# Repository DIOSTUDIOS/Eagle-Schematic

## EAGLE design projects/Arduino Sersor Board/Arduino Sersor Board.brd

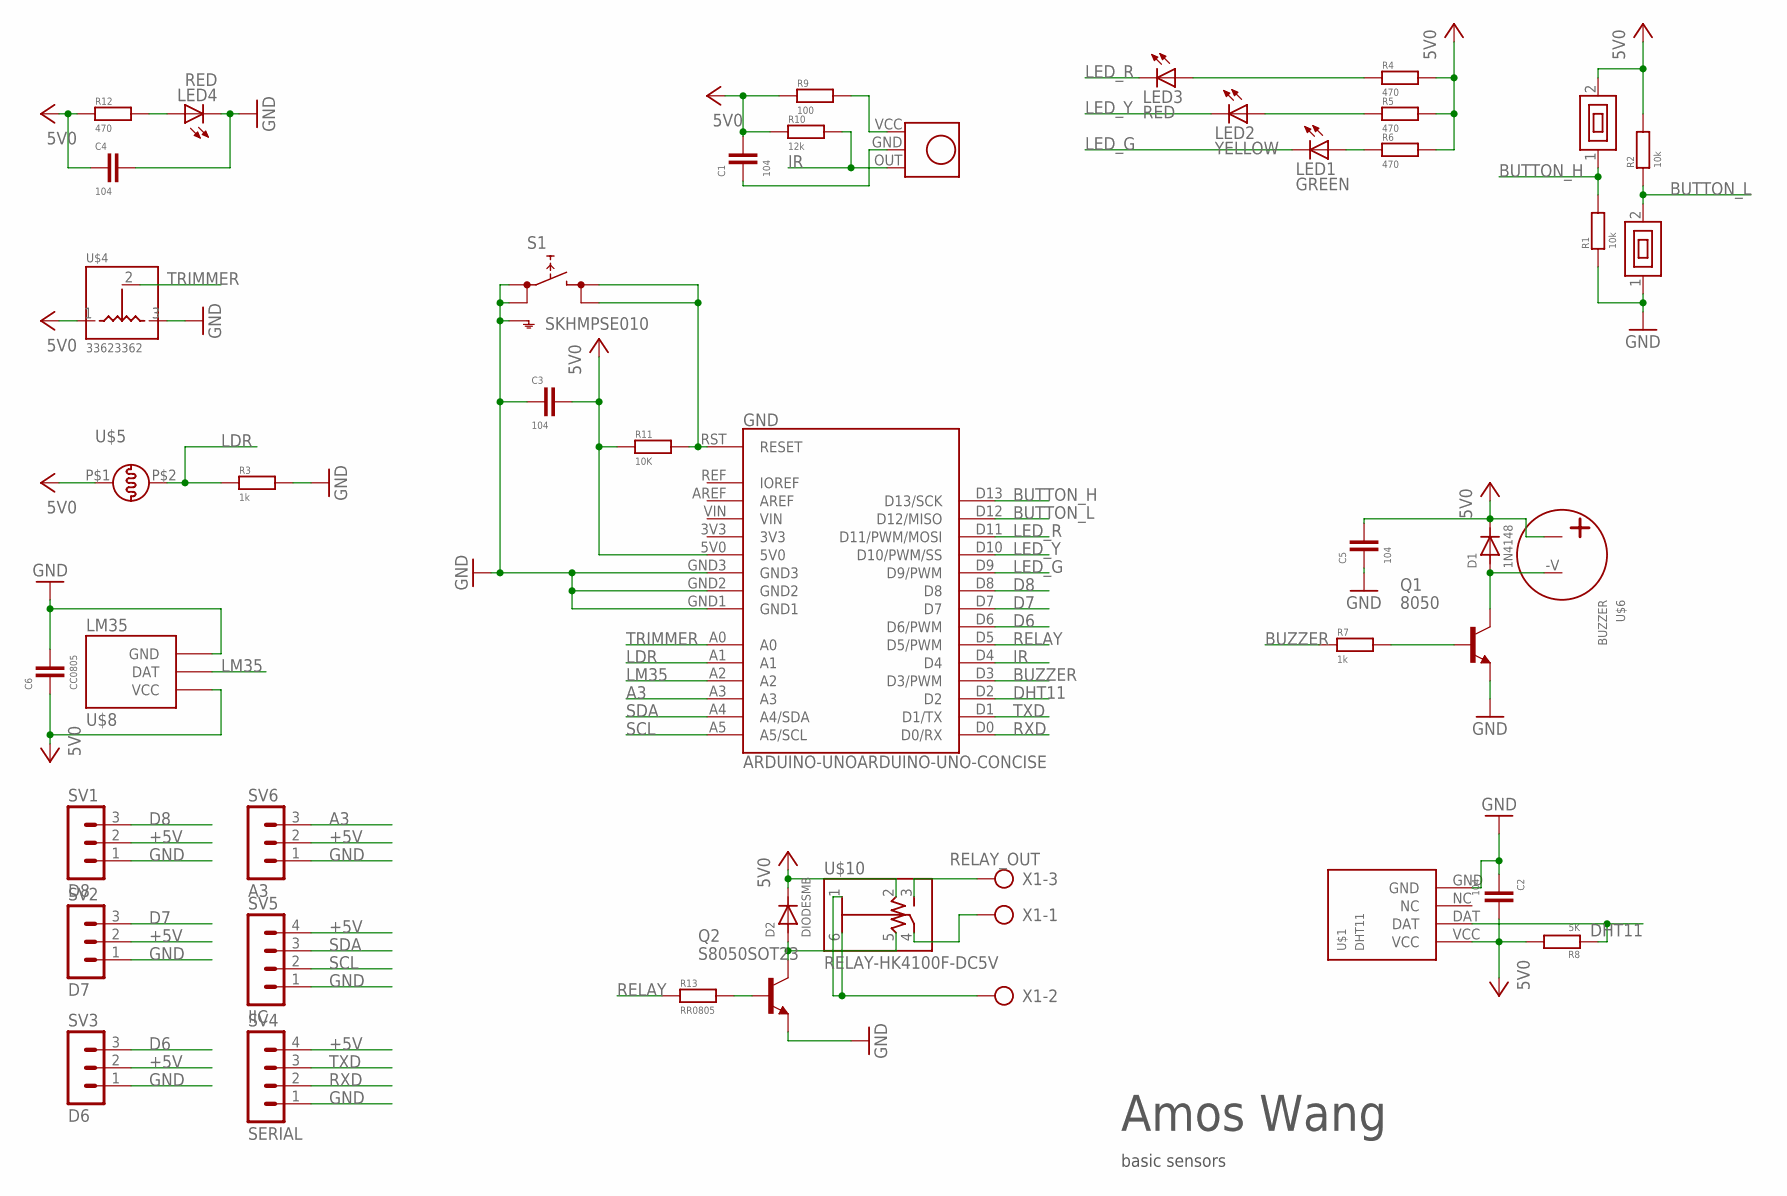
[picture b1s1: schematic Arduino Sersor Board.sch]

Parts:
C1, C2, C3, C4, C5: 104; C0805
C6: CC0805; C0805
D1: 1N4148; SMB
D2: DIODESMB; SMB
GND: ARDUINO-UNOARDUINO-UNO-CONCISE; ARDUINO-UNO
LED1: GREEN; LED2X5
LED2: YELLOW; LED2X5
LED3: RED; LED2X5
LED4: RED; CHIP-LED0805
Q1: 8050; SOT23
Q2: S8050SOT23; SOT23
R1, R2: 10k; R0805
R3, R7: 1k; R0805
R4, R5, R6, R12: 470; R0805
R8: 5K; R0805
R9: 100; R0805
R10: 12k; R0805
R11: 10K; R0805
R13: RR0805; R0805
S1: SKHMPSE010; SKHMPXE010
SV1: D8; MA03-1
SV2: D7; MA03-1
SV3: D6; MA03-1
SV4: SERIAL; MA04-1
SV5: IIC; MA04-1
SV6: A3; MA03-1
U$1: DHT11
U$2, U$3: SMD-36SMD-3*6; SMD-3*6
U$4: 33623362; 3362
U$5: LDR
U$6: BUZZER
U$8: LM35; TO92
U$9: IR-RECIEVER
U$10: RELAY-HK4100F-DC5V
X1: RELAY_OUT; AK500/3

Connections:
+5V: C1.1, C2.1, C3.1, C4.2, C5.1, C6.2, D1.1, D2.1, GND.5V0, R2.2, R4.2, R5.2, R6.2, R8.2, R9.1, R10.1, R11.1, R12.1, SV1.2, SV2.2, SV3.2, SV4.4, SV5.4, SV6.2, U$1.VCC, U$2.2, U$4.1, U$5.P$1, U$6.+V, U$8.1 (VCC), U$10.2
A3: GND.A3, SV6.3
BUTTON_H: GND.D13 (D13/SCK), R1.2, U$2.1
BUTTON_L: GND.D12 (D12/MISO), R2.1, U$3.2
BUZZER: GND.D3 (D3/PWM), R7.1
D6: GND.D6 (D6/PWM), SV3.3
D7: GND.D7, SV2.3
D8: GND.D8, SV1.3
DHT11: GND.D2, R8.1, U$1.DAT
GND: C2.2, C3.2, C4.1, C5.2, C6.1, GND.GND1, GND.GND2, GND.GND3, LED4.C, Q1.E, Q2.E, R1.1, R3.2, S1.1 (1.1), S1.2 (1.2), S1.5 (SH), SV1.1, SV2.1, SV3.1, SV4.1, SV5.1, SV6.1, U$1.GND, U$3.1, U$4.3, U$8.3 (GND)
IR: GND.D4, R10.2, U$9.OUT
LDR: GND.A1, R3.1, U$5.P$2
LED_G: GND.D9 (D9/PWM), LED1.K (C)
LED_R: GND.D11 (D11/PWM/MOSI), LED3.K (C)
LED_Y: GND.D10 (D10/PWM/SS), LED2.K (C)
LM35: GND.A2, U$8.2 (DAT)
unnamed: GND.RST (RESET), R11.2, S1.3 (2.1), S1.4 (2.2)
unnamed: LED4.A, R12.2
unnamed: LED3.A, R4.1
unnamed: LED2.A, R5.1
unnamed: LED1.A, R6.1
unnamed: Q1.B, R7.2
unnamed: D1.2, Q1.C, U$6.-V
unnamed: Q2.B, R13.2
unnamed: D2.2, Q2.C, U$10.5
unnamed: R9.2, U$9.VCC
unnamed: U$10.3, X1.3
unnamed: C1.2, U$9.GND
unnamed: U$10.4, X1.1
unnamed: U$10.1, U$10.6, X1.2
RELAY: GND.D5 (D5/PWM), R13.1
RXD: GND.D0 (D0/RX), SV4.2
SCL: GND.A5 (A5/SCL), SV5.2
SDA: GND.A4 (A4/SDA), SV5.3
TRIMMER: GND.A0, U$4.2
TXD: GND.D1 (D1/TX), SV4.3

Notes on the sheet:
Amos Wang
basic sensors

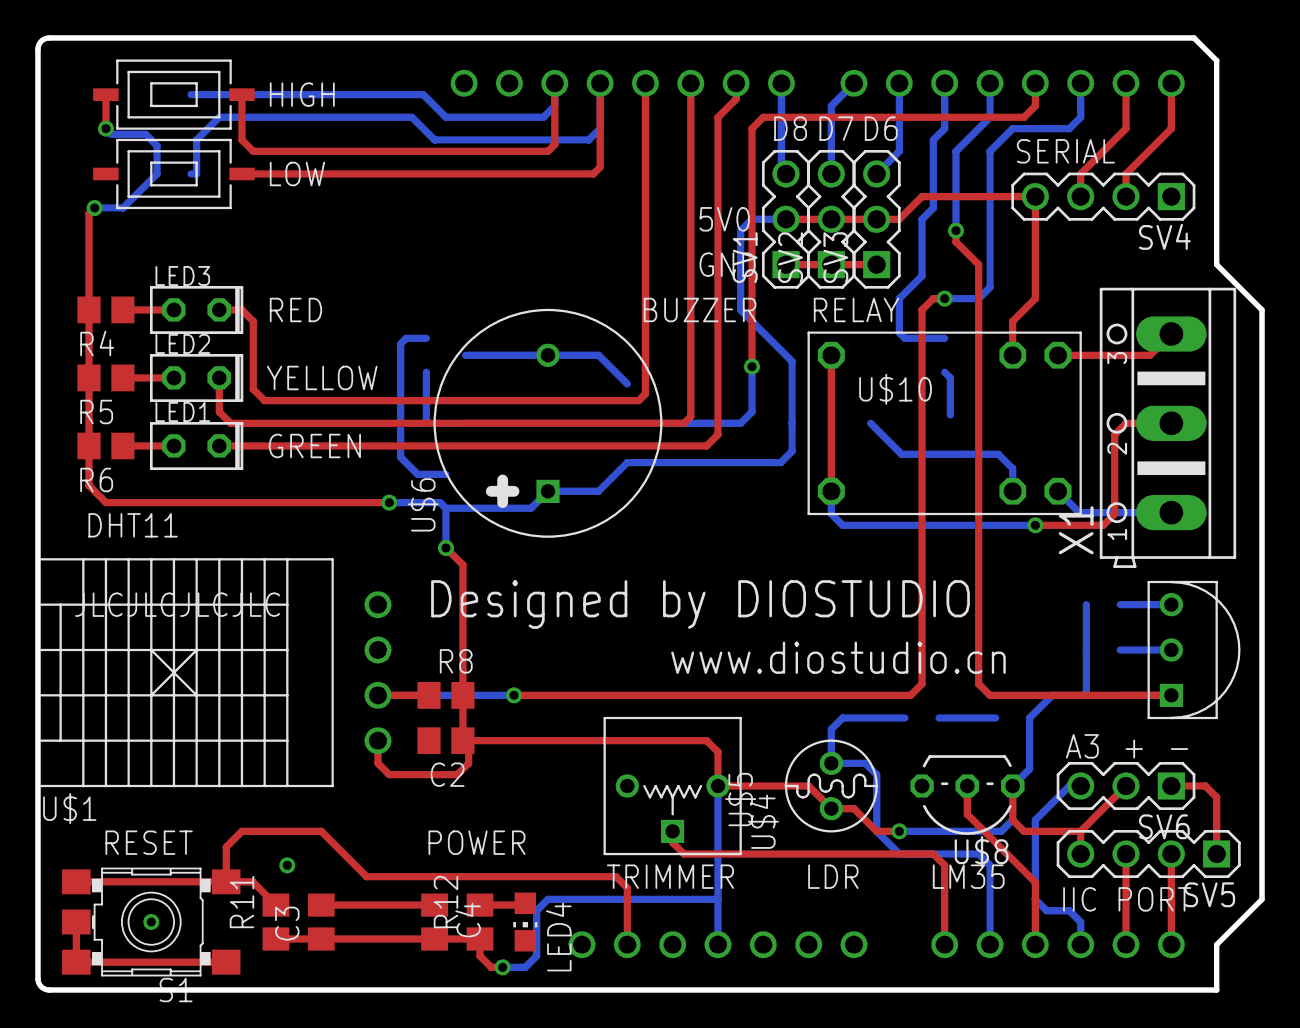
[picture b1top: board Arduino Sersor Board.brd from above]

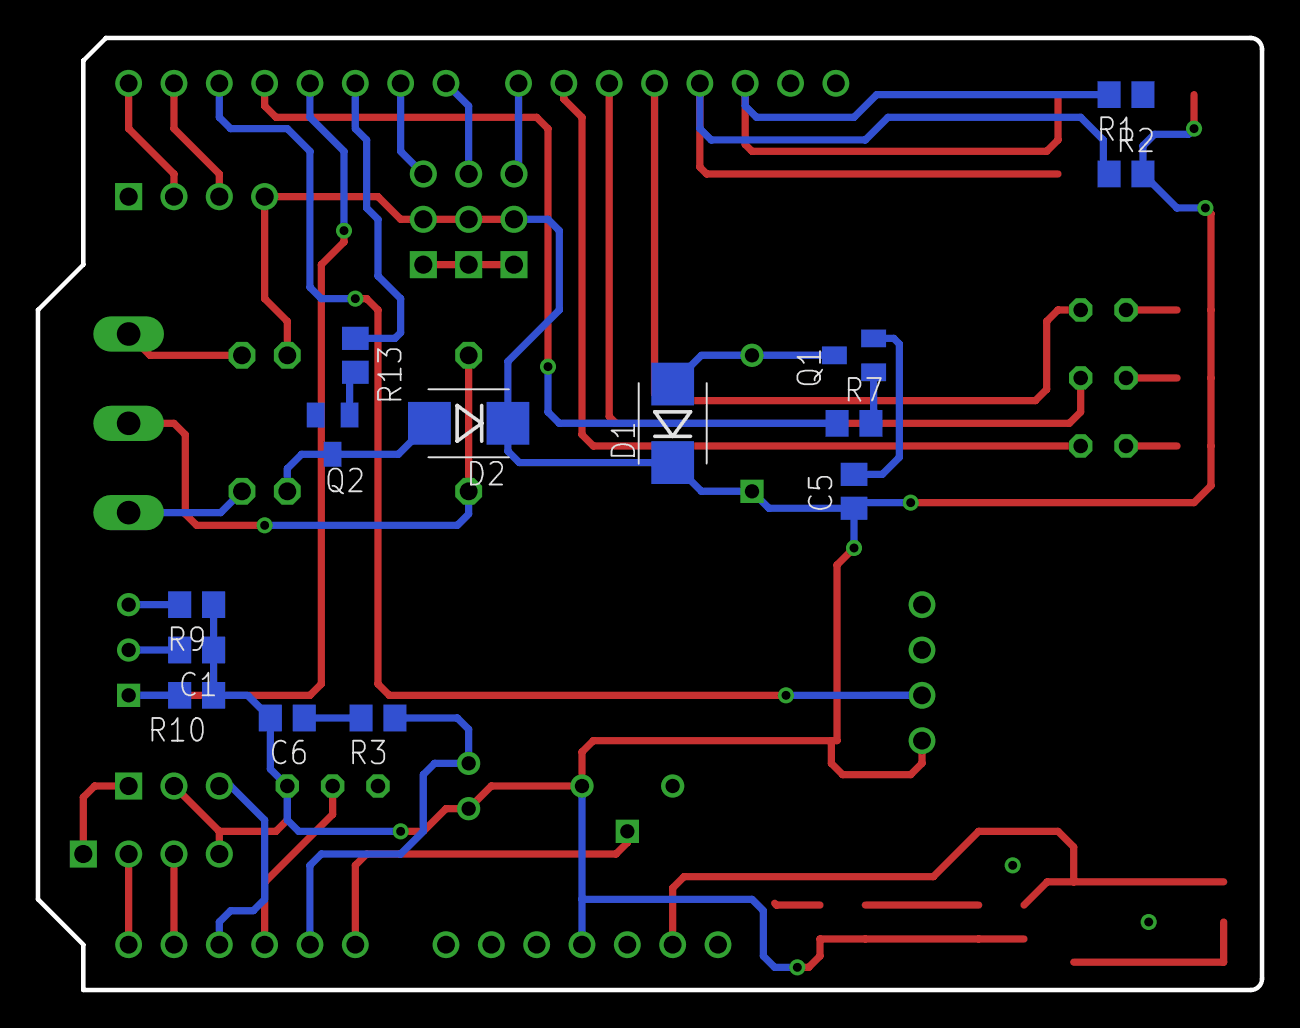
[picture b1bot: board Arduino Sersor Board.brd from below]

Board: 2 copper layers, 68.6 x 53.3 mm, 45 parts (14 on the bottom side), 36 nets.
